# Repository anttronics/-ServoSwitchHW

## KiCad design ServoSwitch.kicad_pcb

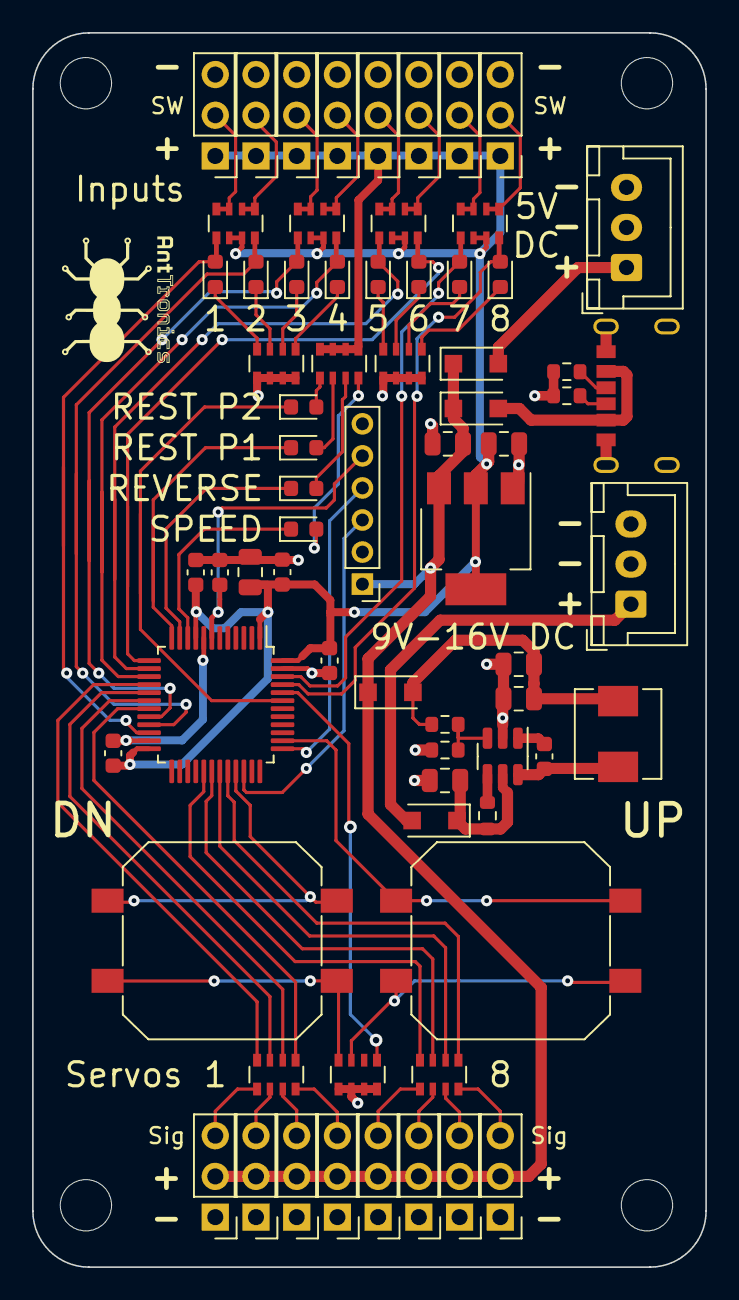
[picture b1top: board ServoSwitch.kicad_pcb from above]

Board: 2 copper layers, 42.0 x 77.0 mm, 73 parts (0 on the bottom side), 70 nets.

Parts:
C1, C7, C9, C10, C12, C13: 22u; C_0805_2012Metric
C2, C3, C4, C5, C6, C8: 100n; C_0603_1608Metric
D1, D2, D7, D8: HXY MOSFET K24; D_SOD-123F
D3, D4, D5, D6, D9, D10, D11, D12, D13, D14, D15, D16: LED_Green; LED_0603_1608Metric
H1, H2, H3, H4: MountingHole; MountingHole_3.2mm_M3
J1: Conn_01x06_Male; PinHeader_1x06_P2.00mm_Vertical
J3: 6V-15V IN; JST_XH_B3B-XH-A_1x03_P2.50mm_Vertical
J4: USB_C_Receptacle_USB2.0; TYPE-C-31-M-17
J5: 5V IN; JST_XH_B3B-XH-A_1x03_P2.50mm_Vertical
J6, J8, J10, J12, J14, J16, J18, J20: ServoInputSW; PinHeader_1x03_P2.54mm_Vertical
J7, J9, J11, J13, J15, J17, J19, J21: ServoOut; PinHeader_1x03_P2.54mm_Vertical
L1: 4.7uH; L_Sunlord_MWSA0518_5.4x5.2mm
R1, R2: 5k1; R_0603_1608Metric
R3, R4: 200k; R_0603_1608Metric
R5: 27k; R_0603_1608Metric
RN1, RN3, RN5, RN6, RN8, RN9, RN10: 1k; R_Array_Convex_4x0603
RN2, RN4, RN7: 10k; R_Array_Convex_4x0603
SW1, SW2: Push Button NO 12mm SMD; SW_Push_1P1T_NO_CK_PTS125Sx43PSMTR
U1: STM32F030C8T6TR; LQFP-48_7x7mm_P0.5mm
U2: EA8212FT6R; SOT-23-6
U3: AMS1117-3.3; SOT-223-3_TabPin2

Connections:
+3V3: C1.1, C2.1, C4.1, C5.1, C6.1, C13.1, J6.1, J8.1, J10.1, J12.1, J14.1, J16.1, J18.1, J20.1, RN2.1 (R1.1), RN2.2 (R2.1), RN2.3 (R3.1), RN2.4 (R4.1), RN3.6 (R3.2), RN3.7 (R2.2), RN6.6 (R3.2), RN6.7 (R2.2), RN9.6 (R3.2), RN9.7 (R2.2), RN10.6 (R3.2), RN10.7 (R2.2), U1.1 (VDD), U1.9 (VDDA), U1.24 (VDD), U1.48 (VDD), U3.2 (VO)
+5V: C9.1, D2.1 (K), D7.1 (K), D8.1 (K), J1.1, J7.2, J9.2, J11.2, J13.2, J15.2, J17.2, J19.2, J21.2, U3.3 (VI)
+VDC: C7.1, D1.1 (K), R3.1, U2.5 (PWR)
/LED_CCW: D3.1 (K), U1.43 (PB7)
/LED_CW: D4.1 (K), U1.12 (PA2)
/LED_DIR: D5.1 (K), U1.11 (PA1)
/LED_SPD: D6.1 (K), U1.10 (PA0)
/NRST: C3.1, J1.5, U1.7 (NRST)
/SW1: D10.2 (A), RN3.5 (R4.2), U1.22 (PB11)
/SW2: D9.2 (A), RN3.8 (R1.2), U1.21 (PB10)
/SW3: D16.2 (A), RN10.5 (R4.2), U1.20 (PB2)
/SW4: D14.2 (A), RN10.8 (R1.2), U1.15 (PA5)
/SW5: D12.2 (A), RN9.5 (R4.2), U1.14 (PA4)
/SW6: D13.2 (A), RN9.8 (R1.2), U1.13 (PA3)
/SW7: D15.2 (A), RN6.5 (R4.2), U1.46 (PB9)
/SW8: D11.2 (A), RN6.8 (R1.2), U1.45 (PB8)
/SWCLK: J1.4, U1.37 (PA14)
/SWDIO: J1.3, U1.34 (PA13)
/SW_DN: SW2.1, U1.33 (PA12)
/SW_UP: SW1.1, U1.38 (PA15)
/Servo1: RN5.4 (R4.1), U1.16 (PA6)
/Servo2: RN5.3 (R3.1), U1.17 (PA7)
/Servo3: RN5.2 (R2.1), U1.18 (PB0)
/Servo4: RN5.1 (R1.1), U1.19 (PB1)
/Servo5: RN8.4 (R4.1), U1.29 (PA8)
/Servo6: RN8.3 (R3.1), U1.30 (PA9)
/Servo7: RN8.2 (R2.1), U1.31 (PA10)
/Servo8: RN8.1 (R1.1), U1.32 (PA11)
/VBUS: D2.2 (A), J4.A9 (VBUS), J4.B9 (VBUS)
/boot: C8.1, U2.1 (BOOT)
/fb: R4.2, R5.1, U2.3 (FBK)
/sw: C8.2, L1.1, U2.6 (SWITCH)
/vout: C10.1, C12.1, D8.2 (A), L1.2, R4.1
GND: C1.2, C2.2, C3.2, C4.2, C5.2, C6.2, C7.2, C9.2, C10.2, C12.2, C13.2, J1.2, J3.2, J3.3, J4.A12 (GND), J4.B12 (GND), J4.S1 (SHIELD), J5.2, J5.3, J6.3, J7.1, J8.3, J9.1, J10.3, J11.1, J12.3, J13.1, J14.3, J15.1, J16.3, J17.1, J18.3, J19.1, J20.3, J21.1, R1.2, R2.1, R5.2, RN1.5 (R4.2), RN1.6 (R3.2), RN1.7 (R2.2), RN1.8 (R1.2), RN4.5 (R4.2), RN4.6 (R3.2), RN4.7 (R2.2), RN4.8 (R1.2), RN7.5 (R4.2), RN7.6 (R3.2), RN7.7 (R2.2), RN7.8 (R1.2), U1.8 (VSSA), U1.23 (VSS), U1.47 (VSS), U2.2 (GND), U3.1 (GND)
unnamed: D1.2 (A), J3.1
unnamed: D3.2 (A), RN2.5 (R4.2)
unnamed: D4.2 (A), RN2.6 (R3.2)
unnamed: D5.2 (A), RN2.7 (R2.2)
unnamed: D6.2 (A), RN2.8 (R1.2)
unnamed: D7.2 (A), J5.1
unnamed: D9.1 (K), RN4.3 (R3.1)
unnamed: D10.1 (K), RN4.4 (R4.1)
unnamed: D11.1 (K), RN7.1 (R1.1)
unnamed: D12.1 (K), RN7.4 (R4.1)
unnamed: D13.1 (K), RN7.3 (R3.1)
unnamed: D14.1 (K), RN4.1 (R1.1)
unnamed: D15.1 (K), RN7.2 (R2.1)
unnamed: D16.1 (K), RN4.2 (R2.1)
unnamed: J4.A5 (CC1), R1.1
unnamed: J4.B5 (CC2), R2.2
unnamed: J6.2, RN3.1 (R1.1), RN3.2 (R2.1)
unnamed: J7.3, RN5.6 (R3.2)
unnamed: J8.2, RN3.3 (R3.1), RN3.4 (R4.1)
unnamed: J9.3, RN5.5 (R4.2)
unnamed: J10.2, RN6.1 (R1.1), RN6.2 (R2.1)
unnamed: J11.3, RN8.8 (R1.2)
unnamed: J12.2, RN9.3 (R3.1), RN9.4 (R4.1)
unnamed: J13.3, RN8.5 (R4.2)
unnamed: J14.2, RN9.1 (R1.1), RN9.2 (R2.1)
unnamed: J15.3, RN8.6 (R3.2)
unnamed: J16.2, RN10.1 (R1.1), RN10.2 (R2.1)
unnamed: J17.3, RN5.8 (R1.2)
unnamed: J18.2, RN6.3 (R3.1), RN6.4 (R4.1)
unnamed: J19.3, RN8.7 (R2.2)
unnamed: J20.2, RN10.3 (R3.1), RN10.4 (R4.1)
unnamed: J21.3, RN5.7 (R2.2)
unnamed: R3.2, U2.4 (RUN)
unnamed: RN1.1 (R1.1), U1.44 (BOOT0)
unnamed: RN1.3 (R3.1), SW1.2
unnamed: RN1.4 (R4.1), SW2.2

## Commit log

2023-12-20 Silkscreen updates
2023-12-20 cleanup according to gitignore
2023-12-20 Rename to ServoSwitch
2023-12-20 Add licence

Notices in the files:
ServoSwitch.kicad_pcb:
SPDX-FileCopyrightText: 2023 Antonios Vamporakis
SPDX-License-Identifier: CERN-OHL-W-2.0+
using it under the terms of the CERN-OHL-W v2 (https:/cern.ch/cern-ohl).
As per CERN-OHL-W v2 section 4.1, should You produce hardware based on
